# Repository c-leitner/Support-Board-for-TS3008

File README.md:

# Support-Board-for-TS3008
Hardware project to add basic functionality for [TS3008 Boards](hhttps://www.tinyosshop.com/index.php?route=product/product&product_id=1119) from TinySine. The PCB is currently untested.

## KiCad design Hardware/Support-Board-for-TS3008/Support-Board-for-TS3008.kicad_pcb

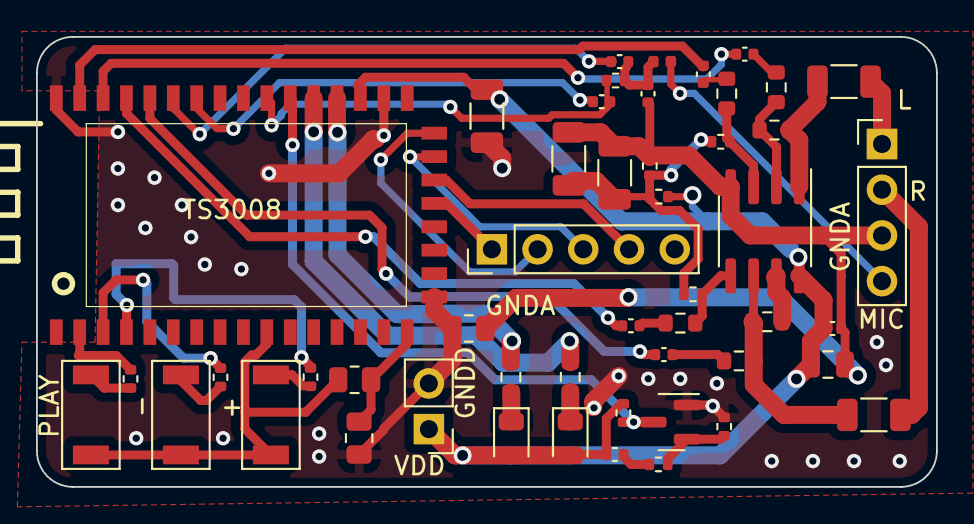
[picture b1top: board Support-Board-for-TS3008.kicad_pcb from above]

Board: 2 copper layers, 50.0 x 25.0 mm, 49 parts (0 on the bottom side), 44 nets.

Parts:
C1, C5, C6, C13, C14: 1UF; C_0402_1005Metric
C2, C9, C15: 220UF; C_1206_3216Metric
C3, C4, C11: 100NF; C_0402_1005Metric
C7, C10: 22UF; C_1206_3216Metric
C8: 15PF; C_0402_1005Metric
C12: 22UF; C_0805_2012Metric
D1: LED_RED; LED_0805_2012Metric
D2: LED_BLUE; LED_0805_2012Metric
J1: Conn_01x02; PinHeader_1x02_P2.54mm_Vertical
J2: Conn_01x05; PinHeader_1x05_P2.54mm_Vertical
J3: Conn_01x04; PinHeader_1x04_P2.54mm_Vertical
L1: 15NH; L_0402_1005Metric
Q1: 2N3904S
R1, R4, R5, R6: 1K; R_0402_1005Metric
R2, R3, R16, R18: 10K; R_0402_1005Metric
R7: 0R; R_0805_2012Metric
R8, R22: NC; R_0805_2012Metric
R9: 470R; R_0603_1608Metric
R10: 75R; R_0603_1608Metric
R11, R12: 100K; R_0402_1005Metric
R13: 2.2K; R_0402_1005Metric
R14, R15, R17, R19, R20, R21: 10K; R_0603_1608Metric
SW1, SW2, SW3: TS-1088R-02026; TS-1088R
U1: TS64215; BluetoothAudioModule(2)-TS64215
U2: SGM358YS/TR; SOIC-8_3.9x4.9mm_P1.27mm

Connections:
/Audio_L: C9.2, J3.1
/Audio_R: C15.2, J3.2
/LED_BLUE: R10.2, U1.29 (LED2)
/LED_RED: R9.1, U1.28 (LED0)
/MFB: Q1.3 (C), R3.1, U1.30 (MFB)
/MIC: J3.4, L1.2
/MIC_AN: C4.2, U1.35 (LINE/MIC_AN)
/MIC_AP: C3.2, U1.34 (LINE/MIC_AP)
/MIC_BIAS: C3.1, R13.2, U1.31 (MIC_BIAS)
/SPK_AN: C5.1, U1.38 (SPK_AN)
/SPK_AP: C6.1, U1.39 (SPK_AP)
/SPK_BN: C13.2, U1.36 (SPK_BN)
/SPK_BP: C14.2, U1.37 (SPK_BP)
/VREF: C7.2, C10.2, R11.1, R12.2, R16.1, R18.1
GNDA: C7.1, C8.2, C10.1, C11.2, C12.2, J3.3, R11.2, R22.1, U2.4 (-Vs)
GNDD: C2.1, J1.2, J2.5, Q1.1 (E), R2.1, R8.1, R22.2, U1.17 (GND1), U1.26 (GND2), U1.40 (GND3)
unnamed: C1.1, R1.1
unnamed: C4.1, C8.1, L1.1, R13.1
unnamed: C5.2, R14.1
unnamed: C6.2, R15.1
unnamed: C9.1, R17.1, U2.1 (OUT_A)
unnamed: C13.1, R20.1
unnamed: C14.1, R21.1
unnamed: C15.1, R19.1, R20.2, U2.6 (-INB)
unnamed: D1.1 (K), R9.2
unnamed: D2.1 (K), R10.1
unnamed: J2.1, U1.21 (MOSI)
unnamed: J2.2, U1.24 (MISO)
unnamed: J2.3, U1.23 (CSB)
unnamed: J2.4, U1.22 (CLK)
unnamed: Q1.2 (B), R1.2, R2.2
unnamed: R4.1, SW1.2
unnamed: R4.2, U1.2 (PIO8)
unnamed: R5.1, SW2.2
unnamed: R5.2, U1.3 (PIO1)
unnamed: R6.1, SW3.2
unnamed: R6.2, U1.4 (PIO0)
unnamed: R7.1, R8.2, U1.16 (SPI_PCM)
unnamed: R7.2, SW1.1, SW2.1, SW3.1, U1.10 (1V8)
unnamed: R14.2, R17.2, U2.2 (-INA)
unnamed: R15.2, R16.2, U2.3 (+INA)
unnamed: R18.2, R21.2, U2.5 (+INB)
unnamed: R19.2, U2.7 (OUTB)
VDD: C1.2, C2.2, C11.1, C12.1, D1.2 (A), D2.2 (A), J1.1, R3.2, R12.1, U1.27 (VBAT), U2.8 (+Vs)

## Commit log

2022-04-29 added shematics
2022-04-29 added datasheets for leds, buttons, board, transistor and amplifier
2022-05-02 added datasheets
2022-05-02 added libs and finished v1 of PCB
2022-05-02 generated gerber files
